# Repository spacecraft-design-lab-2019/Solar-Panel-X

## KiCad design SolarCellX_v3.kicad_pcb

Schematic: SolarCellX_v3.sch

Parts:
C1: 1.0uF; C_0402_1005Metric
C2, C5, C9, C10, C13: 0.1uF; C_0402_1005Metric
C3, C8: 4.7uF; C_0402_1005Metric
C4: 10nF; C_0402_1005Metric
C6, C11, C12, C14: 100uF; C_0603_1608Metric
C7: 22uF; C_0402_1005Metric
D1: SDM20U40-7; SOD523
D2, D3: MSS1P4-M3_89A; MICROSMP; Manufacturer_Part_Number MSS1P4-M3/89A; Mouser Part Number 625-MSS1P4-M3
D4, D5: SBDiode; SB Diode
J1: XF2M-1015-1A; Manufacturer_Part_Number XF2M-1015-1A; Mouser Part Number 653-XF2M-1015-1A
L1: 22uH-LPS4018-223MR; LPS4018
L2: 10uH-LPS4018-103MR; LPS4018
R1, R2, R3, R4, R12, R13, R14, R15, R16, R17, R18, R19: 0; R_0402_1005Metric
R5: 7.32M; R_0402_1005Metric
R6: 5.62M; R_0402_1005Metric
R7: 374K; R_0402_1005Metric
R8, R10: 8.25M; R_0402_1005Metric
R9: 4.53M; R_0402_1005Metric
R11: 4.75M; R_0402_1005Metric
SC1, SC2, SC3, SC4, SC5, SC6, SC7, SC8: SolarCell_Small; KXOB25-05X3F
TP1, TP2, TP3, TP4: TP; TestPoint_THTPad_D1.0mm_Drill0.5mm
U2: Value; QFN50P350X350X100-21N-D
U3: TSL2561; Manufacturer_Part_Number TSL2561; Mouser Part Number N/A

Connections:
+3V3: C5.2, C13.1, C14.1, D2.1, J1.6, R12.2, TP1.1, U3.1
/VSOLAR_FULL: D3.2, D4.1 (NEG), SC1.1 (V+), SC2.1 (V+), SC3.1 (V+), SC4.1 (V+), TP4.1
/coil: R2.2, R3.1, R4.2, R19.1
BATT_N: J1.2, R18.1
BATT_P: J1.1, R17.1
COIL_N: J1.9, R4.1, R19.2
COIL_P: J1.10, R2.1, R3.2
GND: C1.2, C2.2, C3.2, C4.2, C5.1, C6.2, C7.2, C8.2, C9.2, C10.2, C11.2, C12.2, C13.2, C14.2, D1.A, D5.2 (POS), J1.7, J1.8, R6.1, R9.1, R11.1, R13.1, R15.1, R18.2, SC5.2 (V-), SC6.2 (V-), SC7.2 (V-), SC8.2 (V-), TP2.1, U2.1 (VSS_2), U2.5 (EN_N), U2.9 (NC_2), U2.15 (VSS), U2.17 (NC), U2.21 (PAD), U3.3
unnamed: C4.1, U2.4 (VREF_SAMP)
unnamed: C7.1, C10.1, C12.1, D2.2, L2.2, U2.14 (VOUT)
unnamed: C8.1, C9.1, C11.1, R16.1, U2.19 (VSTOR)
unnamed: D4.2 (POS), D5.1 (NEG), SC1.2 (V-), SC2.2 (V-), SC3.2 (V-), SC4.2 (V-), SC5.1 (V+), SC6.1 (V+), SC7.1 (V+), SC8.1 (V+)
unnamed: L1.2, U2.20 (LBOOST)
unnamed: L2.1, U2.16 (LBUCK)
unnamed: R5.1, R6.2, U2.7 (VBAT_OV)
unnamed: R7.1, R8.2, U2.10 (OK_HYST)
unnamed: R8.1, R9.2, U2.11 (OK_PROG)
unnamed: R10.1, R11.2, U2.12 (VOUT_SET)
unnamed: R5.2, R7.2, R10.2, U2.8 (VRDIV)
unnamed: R12.1, R13.2, U3.2
unnamed: R14.1, R15.2, R16.2, U2.3 (VOC_SAMP)
SCL1: J1.4, U3.4
SDA1: J1.3, U3.6
VBAT: C6.1, R17.2, TP3.1, U2.18 (VBAT)
VBAT_OK: R1.1, U2.13 (VBAT_OK)
VOUT_EN: C1.1, R1.2, U2.6 (VOUT_EN)
VSOLAR: C2.1, C3.1, D1.C, D3.1, L1.1, R14.2, U2.2 (VIN_DC)

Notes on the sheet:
DNI
ZENER
VOUT 3.31
80% MPPT
VBAT_OK ON: 3.51V OFF: 3.42V
Imin=280uA
External Power Source Input (Solar)
External energy storage Input/Output
BQ25570RGRR
Energy Harvesting IC
VBAT_OV 4.2V
Sets of resistor dividers should = 13MOhm
VOUT=1.21V*((ROUT2+ROUT1)/ROUT1)
MPPT Set Resistors
Flat Flex Connector
COIL+
COIL-
Clockwise (while facing layer 1)
Test Points

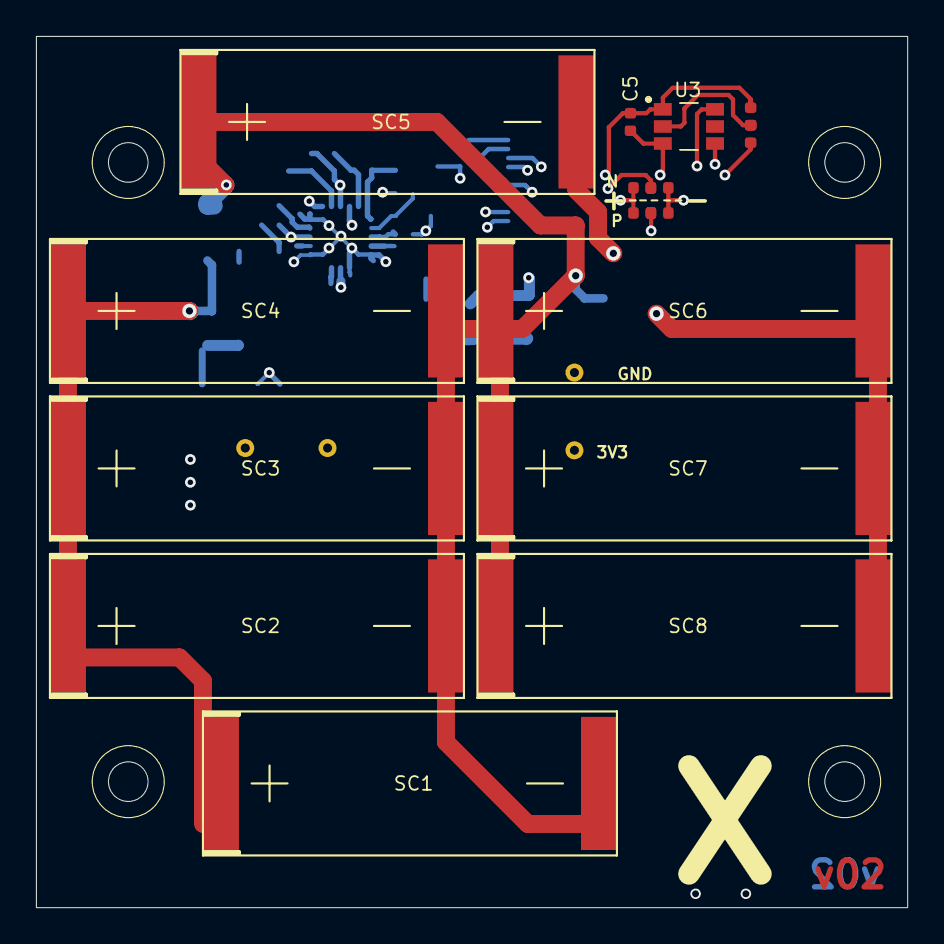
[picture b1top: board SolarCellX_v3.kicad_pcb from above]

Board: 6 copper layers, 48.4 x 48.4 mm, 55 parts (0 on the bottom side), 27 nets.

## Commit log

2019-10-21 SolarCellX_v1 initial upload
    This is just to add the footprints and libraries for the solar cells and diodes to the Git - the board layout is not finished!
2019-10-21 Finished the trace layout
2019-10-23 Added the mounting & USB hole
2019-10-23 Updated Board Cuts and Solar Cell choice
    The traces & Magnetorquers haven't been put in yet - still finalizing hole layout with structures
2019-10-24 Added the first layer of the magnetorquer
2019-10-24 Finished the Magnetorquer
2019-10-25 Cleaned up the Magnetorquer and added labels
2019-10-25 making libraries locally referenced for easy import
2019-10-25 preparing to import misc-circuits
2019-10-25 circuits added and coil connection made
2019-10-25 cleanup- still need to add logo
2019-10-25 X and Z panels are ready
2019-10-26 zipped fabrication files for all but +Y
2019-10-26 JLCPCB fab output
2019-10-26 adding interactive BOMs for +/-X,-Y,+-Z
2019-10-28 generating 3D CAD
2019-10-28 Added first revision of step for board - missing one connector.
2019-11-01 y+ BOM
2019-11-01 stencil outputs
2019-12-10 Extended pads and added flatflex labels
2019-12-20 v01 order + repo overhaul
2020-02-10 fixed pcb - schematic inconsistencies
2020-02-19 moved solar panel and sun sensor. Fixed PCB design rules
2020-02-20 updated 3d footprint paths and generated new step file
2020-02-23 moved diode to fix mechanical collision
2020-02-28 Changed magnetorquer coils
2020-02-29 design review and generated gerbers
2020-03-01 added fiducials, regenerated 3d model and gerbers
